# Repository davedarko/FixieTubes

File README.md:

# FixieTubes

visit https://hackaday.io/project/1886-fixietube-clock for the documentation

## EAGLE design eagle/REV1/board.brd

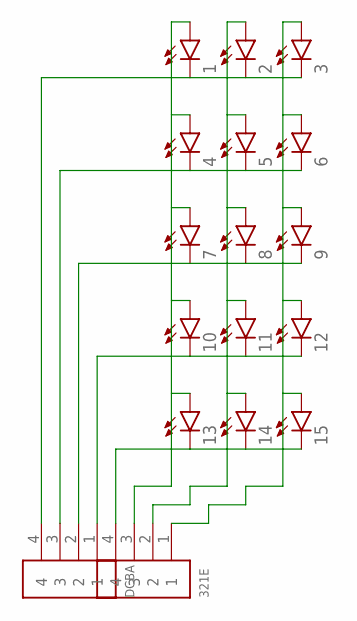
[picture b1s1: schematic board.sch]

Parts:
1, 2, 3, 4, 5, 6, 7, 8, 9, 10, 11, 12, 13, 14, 15: LED3MM
321E: 1X4-BIG; 1X04-BIG
DCBA: 1X4-BIG; 1X04-BIG

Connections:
1: 2.A, 5.A, 8.A, 11.A, 14.A, 321E.2
unnamed: 1.K (C), 2.K (C), 3.K (C), DCBA.4
unnamed: 4.K (C), 5.K (C), 6.K (C), DCBA.3
unnamed: 7.K (C), 8.K (C), 9.K (C), DCBA.2
unnamed: 10.K (C), 11.K (C), 12.K (C), DCBA.1
unnamed: 13.K (C), 14.K (C), 15.K (C), 321E.4
unnamed: 1.A, 4.A, 7.A, 10.A, 13.A, 321E.3
unnamed: 3.A, 6.A, 9.A, 12.A, 15.A, 321E.1

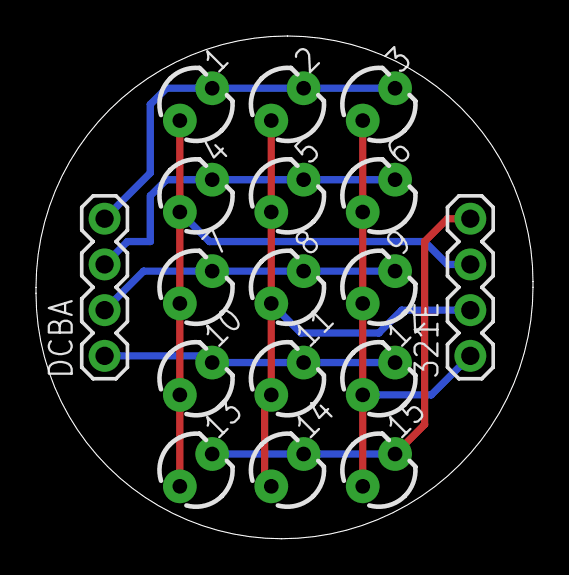
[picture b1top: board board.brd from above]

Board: 2 copper layers, 27.6 x 27.9 mm, 17 parts (0 on the bottom side), 8 nets.

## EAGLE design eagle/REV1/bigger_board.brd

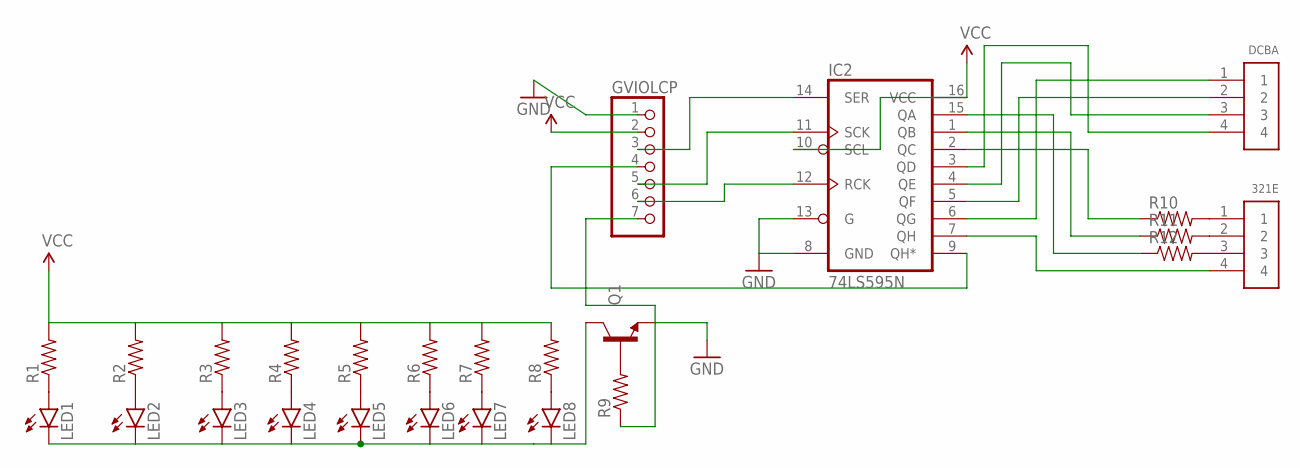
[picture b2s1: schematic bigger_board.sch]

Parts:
321E: 1X4-BIG; 1X04-BIG
DCBA: 1X4-BIG; 1X04-BIG
GVIOLCP: PINHD-1X7; 1X07
IC2: 74LS595N; DIL16
LED1, LED2, LED3, LED4, LED5, LED6, LED7, LED8: LED3MM
Q1: TRANSISTOR_NPNBC547; TO-92-AMMO
R1, R2, R3, R4, R5, R6, R7, R8, R9, R10, R11, R12: RESISTOR1206; 1206

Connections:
GND: GVIOLCP.1, IC2.8 (GND), IC2.13 (G), Q1.3 (E)
unnamed: IC2.15 (QA), R12.1
unnamed: IC2.1 (QB), R11.1
unnamed: IC2.2 (QC), R10.1
unnamed: DCBA.1, IC2.6 (QG)
unnamed: DCBA.2, IC2.5 (QF)
unnamed: DCBA.3, IC2.4 (QE)
unnamed: DCBA.4, IC2.3 (QD)
unnamed: 321E.4, IC2.7 (QH)
unnamed: LED3.A, R3.1
unnamed: LED4.A, R4.1
unnamed: LED5.A, R5.1
unnamed: LED6.A, R6.1
unnamed: LED7.A, R7.1
unnamed: LED8.A, R8.1
unnamed: LED1.A, R1.1
unnamed: LED2.A, R2.1
unnamed: Q1.2 (B), R9.2
unnamed: GVIOLCP.7, R9.1
unnamed: GVIOLCP.3, IC2.14 (SER)
unnamed: GVIOLCP.4, IC2.9 (QH*)
unnamed: GVIOLCP.5, IC2.11 (SCK)
unnamed: GVIOLCP.6, IC2.12 (RCK)
unnamed: 321E.3, R12.2
unnamed: 321E.1, R10.2
unnamed: 321E.2, R11.2
unnamed: LED1.K (C), LED2.K (C), LED3.K (C), LED4.K (C), LED5.K (C), LED6.K (C), LED7.K (C), LED8.K (C), Q1.1 (C)
VCC: GVIOLCP.2, IC2.10 (SCL), IC2.16 (VCC), R1.2, R2.2, R3.2, R4.2, R5.2, R6.2, R7.2, R8.2

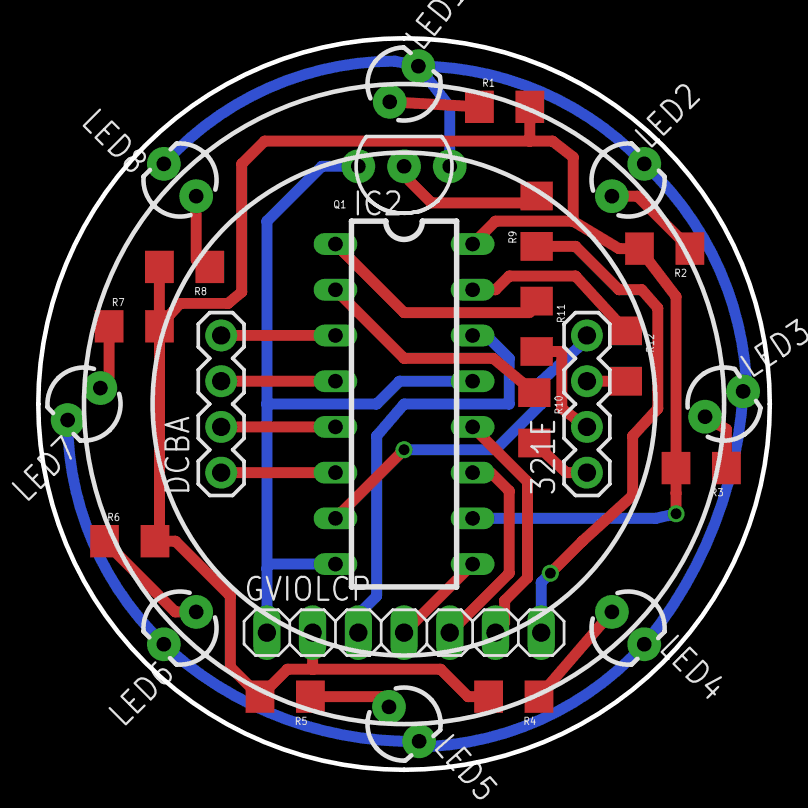
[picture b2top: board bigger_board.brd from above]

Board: 2 copper layers, 40.6 x 40.6 mm, 25 parts (0 on the bottom side), 28 nets.

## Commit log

2015-03-08 eagle files
2015-03-08 schematics
2016-06-14 turn off blue lights between 23 and 7
2016-06-15 performance
2016-06-16 stuff
2018-01-20 updated revisions

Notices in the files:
parts and their libraries:
SparkFun-LED: Licensing: Creative Commons ShareAlike 4.0 International - https://creativecommons.org/licenses/by-sa/4.0
